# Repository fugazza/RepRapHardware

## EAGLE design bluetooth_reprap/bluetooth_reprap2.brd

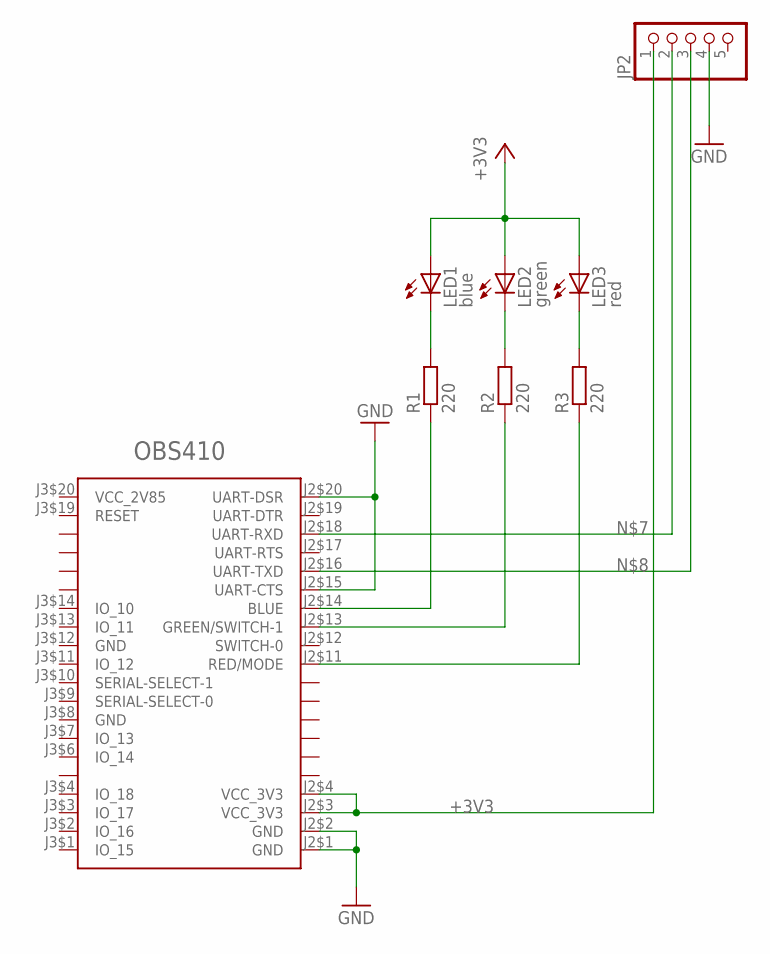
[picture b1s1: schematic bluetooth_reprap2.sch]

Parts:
JP2: PINHD-1X5; 1X05
LED1: blue; LED5MM
LED2: green; LED5MM
LED3: red; LED5MM
R1, R2, R3: 220; 0207/10
U$1: OBS410; SAMTEC-FSI-120-03-G-D-M-AB

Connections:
+3V3: JP2.1, LED1.A, LED2.A, LED3.A, U$1.J2$3 (VCC_3V3), U$1.J2$4 (VCC_3V3)
GND: JP2.4, U$1.J2$1 (GND), U$1.J2$2 (GND), U$1.J2$15 (UART-CTS), U$1.J2$20 (UART-DSR), U$1.J3$8 (GND), U$1.J3$12 (GND)
unnamed: LED1.K (C), R1.2
unnamed: LED2.K (C), R2.2
unnamed: LED3.K (C), R3.2
unnamed: R1.1, U$1.J2$14 (BLUE)
unnamed: R2.1, U$1.J2$13 (GREEN/SWITCH-1)
unnamed: R3.1, U$1.J2$11 (RED/MODE)
unnamed: JP2.2, U$1.J2$18 (UART-RXD)
unnamed: JP2.3, U$1.J2$16 (UART-TXD)

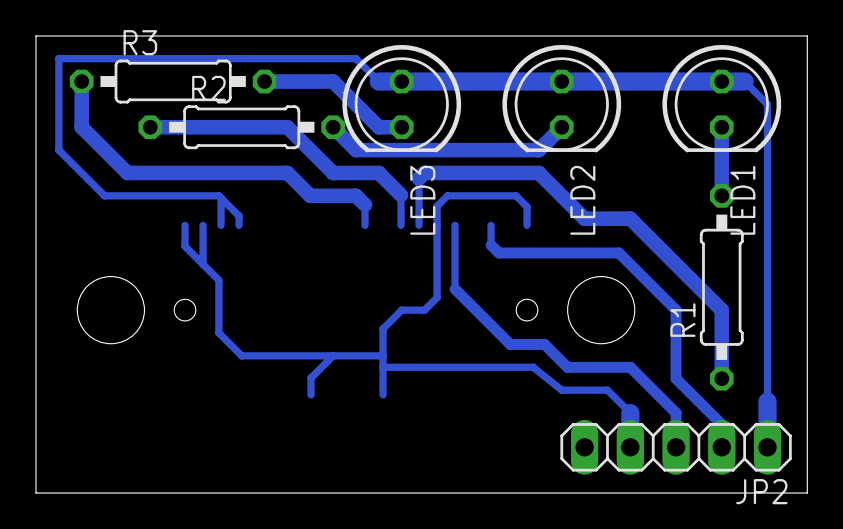
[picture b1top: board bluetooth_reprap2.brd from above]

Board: 2 copper layers, 42.9 x 25.4 mm, 8 parts (1 on the bottom side), 10 nets.

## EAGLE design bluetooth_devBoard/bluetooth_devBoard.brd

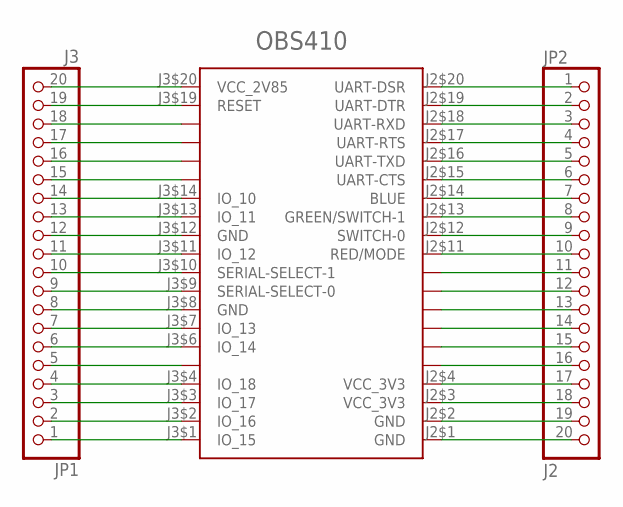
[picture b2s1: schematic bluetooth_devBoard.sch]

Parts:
JP1: J3; 1X20
JP2: J2; 1X20
U$1: OBS410; SAMTEC-FSI-120-03-G-D-M-AB

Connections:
GND: JP2.19, JP2.20, U$1.J2$1 (GND), U$1.J2$2 (GND)
unnamed: JP1.20, U$1.J3$20 (VCC_2V85)
unnamed: JP1.19, U$1.J3$19 (RESET)
unnamed: JP1.18, U$1.J3$18
unnamed: JP1.17, U$1.J3$17
unnamed: JP1.16, U$1.J3$16
unnamed: JP1.15, U$1.J3$15
unnamed: JP1.14, U$1.J3$14 (IO_10)
unnamed: JP1.13, U$1.J3$13 (IO_11)
unnamed: JP1.12, U$1.J3$12 (GND)
unnamed: JP1.11, U$1.J3$11 (IO_12)
unnamed: JP1.10, U$1.J3$10 (SERIAL-SELECT-1)
unnamed: JP1.9, U$1.J3$9 (SERIAL-SELECT-0)
unnamed: JP1.8, U$1.J3$8 (GND)
unnamed: JP1.7, U$1.J3$7 (IO_13)
unnamed: JP1.6, U$1.J3$6 (IO_14)
unnamed: JP1.5, U$1.J3$5
unnamed: JP1.4, U$1.J3$4 (IO_18)
unnamed: JP1.3, U$1.J3$3 (IO_17)
unnamed: JP1.2, U$1.J3$2 (IO_16)
unnamed: JP1.1, U$1.J3$1 (IO_15)
unnamed: JP2.1, U$1.J2$20 (UART-DSR)
unnamed: JP2.2, U$1.J2$19 (UART-DTR)
unnamed: JP2.3, U$1.J2$18 (UART-RXD)
unnamed: JP2.4, U$1.J2$17 (UART-RTS)
unnamed: JP2.5, U$1.J2$16 (UART-TXD)
unnamed: JP2.6, U$1.J2$15 (UART-CTS)
unnamed: JP2.7, U$1.J2$14 (BLUE)
unnamed: JP2.8, U$1.J2$13 (GREEN/SWITCH-1)
unnamed: JP2.9, U$1.J2$12 (SWITCH-0)
unnamed: JP2.10, U$1.J2$11 (RED/MODE)
unnamed: JP2.11, U$1.J2$10
unnamed: JP2.12, U$1.J2$9
unnamed: JP2.13, U$1.J2$8
unnamed: JP2.14, U$1.J2$7
unnamed: JP2.15, U$1.J2$6
unnamed: JP2.16, U$1.J2$5
unnamed: JP2.17, U$1.J2$4 (VCC_3V3)
VCC_3V3: JP2.18, U$1.J2$3 (VCC_3V3)

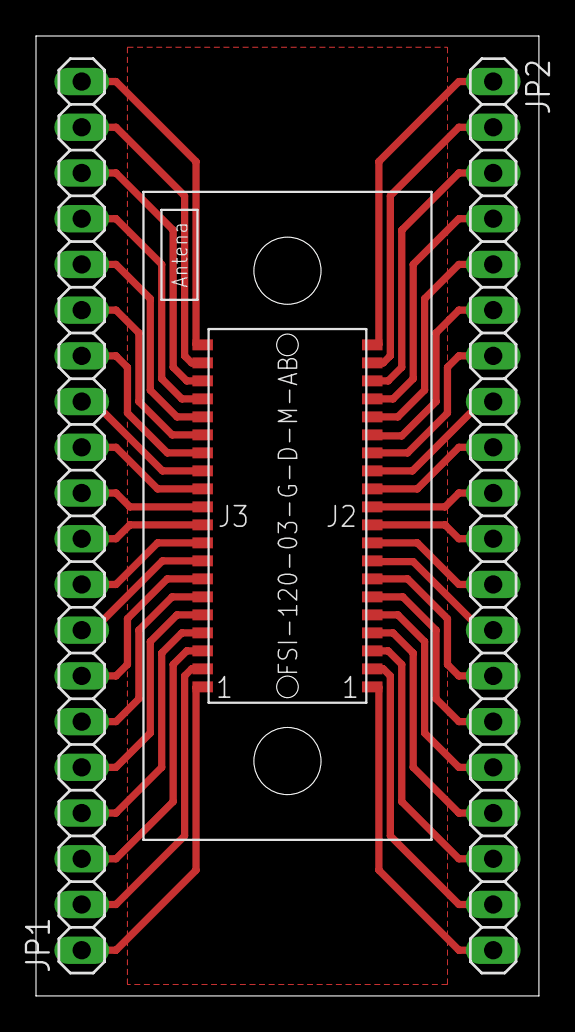
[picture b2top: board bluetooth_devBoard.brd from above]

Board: 1 copper layer, 27.9 x 53.3 mm, 3 parts (0 on the bottom side), 39 nets.

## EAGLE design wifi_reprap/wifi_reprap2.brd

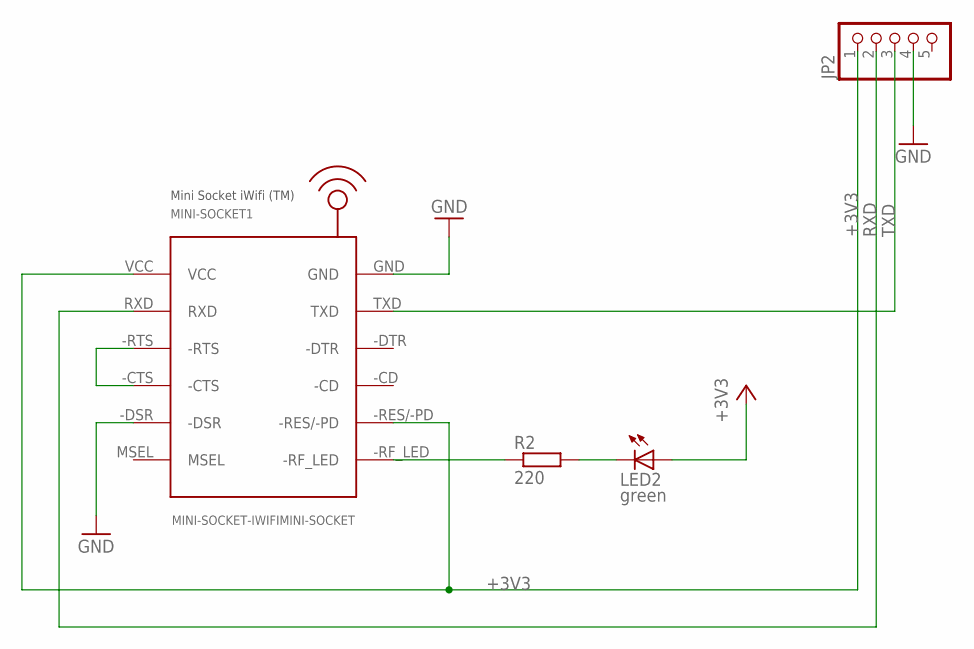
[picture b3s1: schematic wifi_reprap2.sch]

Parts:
JP2: PINHD-1X5; 1X05
LED2: green; LED5MM
MINI-SOCKET1: MINI-SOCKET-IWIFIMINI-SOCKET; MINI-SOCKET-IWIFI
R2: 220; 0207/10

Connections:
+3V3: JP2.1, LED2.A, MINI-SOCKET1.-RES/-PD, MINI-SOCKET1.VCC
GND: JP2.4, MINI-SOCKET1.-DSR, MINI-SOCKET1.GND
unnamed: LED2.K (C), R2.2
unnamed: MINI-SOCKET1.-RF_LED, R2.1
unnamed: MINI-SOCKET1.-CTS, MINI-SOCKET1.-RTS
RXD: JP2.2, MINI-SOCKET1.RXD
TXD: JP2.3, MINI-SOCKET1.TXD

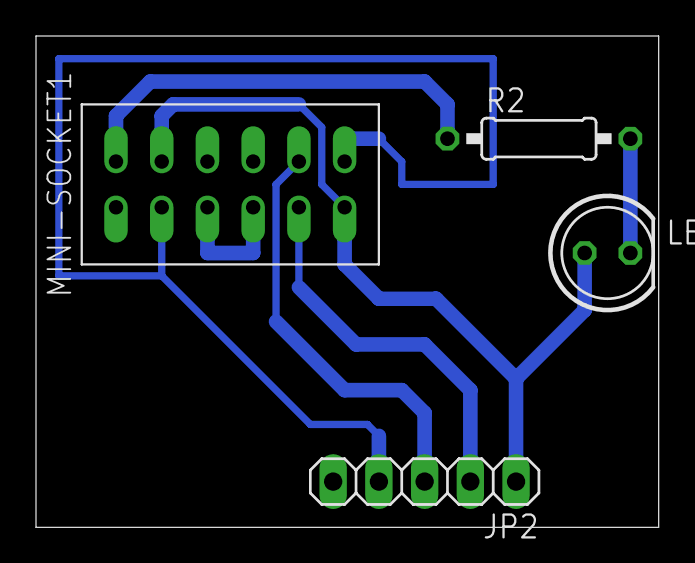
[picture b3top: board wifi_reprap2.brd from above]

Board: 2 copper layers, 34.6 x 27.3 mm, 4 parts (0 on the bottom side), 7 nets.

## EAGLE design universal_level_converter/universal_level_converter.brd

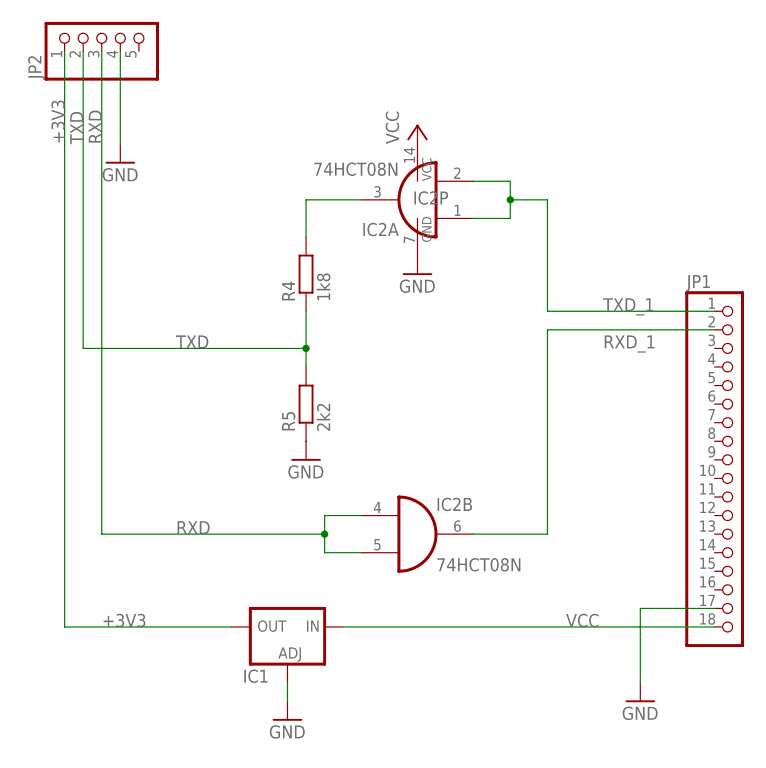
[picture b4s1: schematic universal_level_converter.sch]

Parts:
IC1: LM138-TL; TO220L1
IC2: 74HCT08N; DIL14
JP1: PINHD-1X18; 1X18
JP2: PINHD-1X5; 1X05
R4: 1k8; 0207/10
R5: 2k2; 0207/10

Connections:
+3V3: IC1.2 (OUT), JP2.1
GND: IC1.1 (ADJ), IC2.7 (GND), JP1.17, JP2.4, R5.1
unnamed: IC2.3 (O), R4.2
RXD: IC2.4 (I0), IC2.5 (I1), JP2.3
RXD_1: IC2.6 (O), JP1.2
TXD: JP2.2, R4.1, R5.2
TXD_1: IC2.1 (I0), IC2.2 (I1), JP1.1
VCC: IC1.3 (IN), IC2.14 (VCC), JP1.18

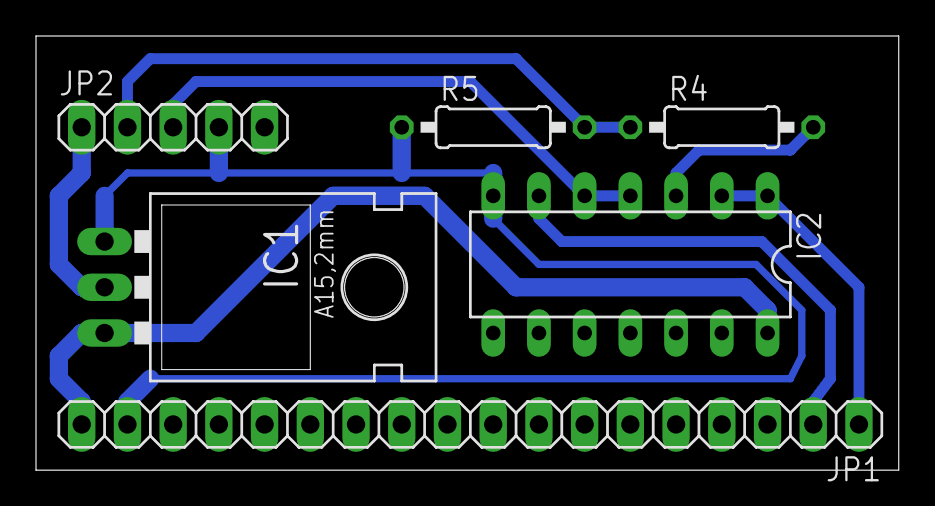
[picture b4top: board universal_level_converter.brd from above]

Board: 2 copper layers, 47.9 x 24.1 mm, 6 parts (0 on the bottom side), 8 nets.
